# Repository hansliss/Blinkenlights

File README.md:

# Blinkenlights
65C02 adapter for 6502 socket plus blinkenlights on all address and data lines

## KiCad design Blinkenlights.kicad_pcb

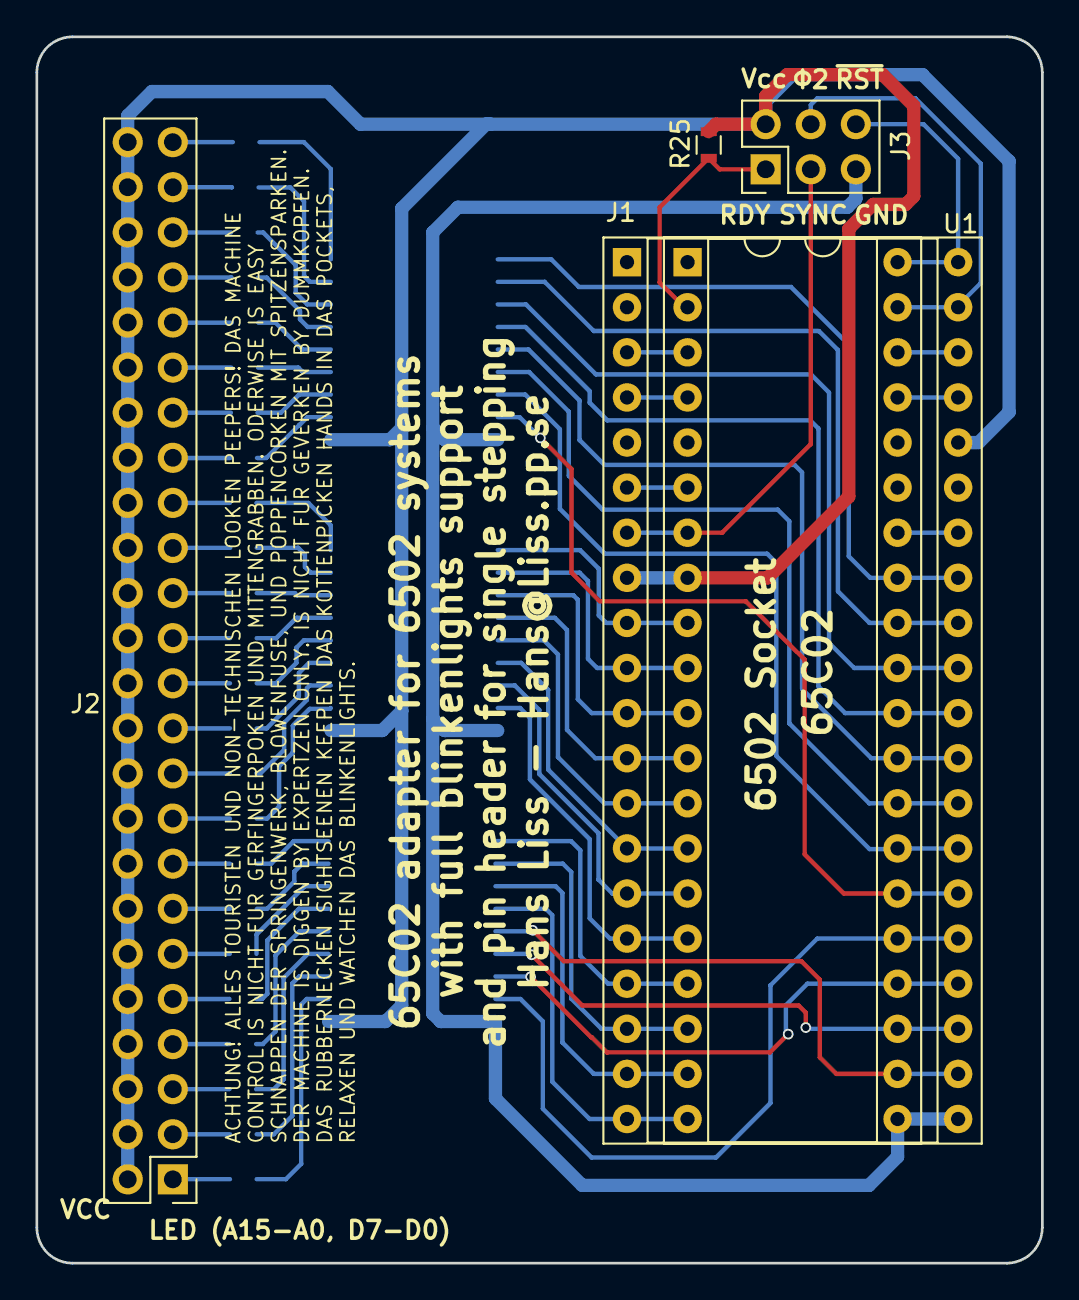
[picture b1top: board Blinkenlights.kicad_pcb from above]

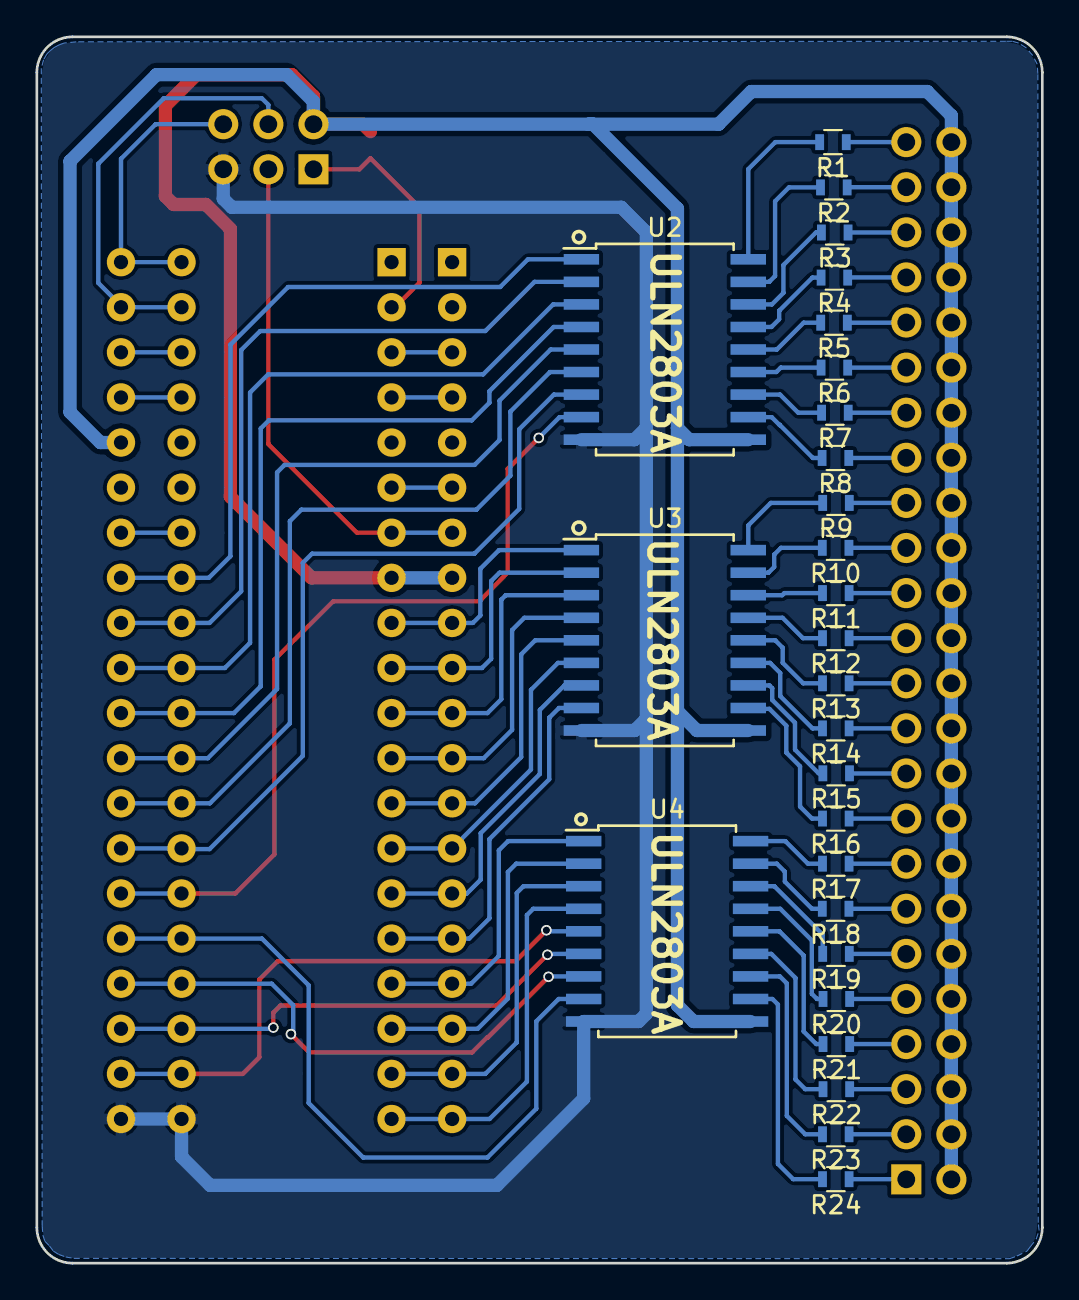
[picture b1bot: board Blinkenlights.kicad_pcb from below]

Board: 2 copper layers, 56.6 x 69.1 mm, 32 parts (27 on the bottom side), 84 nets.

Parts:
J1: 6502_socket; DIP-40_W15.24mm_Socket
J2: Conn_02x24_Odd_Even; Pin_Header_Straight_2x24_Pitch2.54mm
J3: Conn_02x03_Odd_Even; Pin_Header_Straight_2x03_Pitch2.54mm
R1, R2, R3, R4, R5, R6, R7, R8, R9, R10, R11, R12, R13, R14, R15, R16, R17, R18, R19, R20, R21, R22, R23, R24: 4k7; R_0603
R25: 10k; R_0603
U1: WD65C02; DIP-40_W15.24mm_Socket
U2, U3, U4: ULN2803A; SOIC-18W_7.5x11.6mm_Pitch1.27mm

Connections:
/RDY: J3.1, R25.2, U1.2
/SYNC: J1.7, J3.3, U1.7
GND: J1.21, J3.5, U1.21, U2.9, U3.9, U4.9
unnamed: J1.3, U1.3
unnamed: J1.4, U1.4
unnamed: J1.6, U1.6
unnamed: J1.9, U1.9, U3.1
unnamed: J1.10, U1.10, U3.2
unnamed: J1.11, U1.11, U3.3
unnamed: J1.12, U1.12, U3.4
unnamed: J1.13, U1.13, U3.5
unnamed: J1.14, U1.14, U3.6
unnamed: J1.15, U1.15, U3.7
unnamed: J1.16, U1.16, U3.8
unnamed: J1.17, U1.17, U4.1
unnamed: J1.18, U1.18, U4.2
unnamed: J1.19, U1.19, U4.3
unnamed: J1.20, U1.20, U4.4
unnamed: J1.22, U1.22, U4.5
unnamed: J1.23, U1.23, U4.6
unnamed: J1.24, U1.24, U4.7
unnamed: J1.25, U1.25, U4.8
unnamed: J1.26, U1.26, U2.8
unnamed: J1.27, U1.27, U2.7
unnamed: J1.28, U1.28, U2.6
unnamed: J1.29, U1.29, U2.5
unnamed: J1.30, U1.30, U2.4
unnamed: J1.31, U1.31, U2.3
unnamed: J1.32, U1.32, U2.2
unnamed: J1.33, U1.33, U2.1
unnamed: J1.34, U1.34
unnamed: J1.37, U1.37
unnamed: J1.38, U1.38
unnamed: J1.39, J3.4, U1.39
unnamed: J1.40, J3.6, U1.40
unnamed: J2.1, R24.1
unnamed: J2.3, R23.1
unnamed: J2.5, R22.1
unnamed: J2.7, R21.1
unnamed: J2.9, R20.1
unnamed: J2.11, R19.1
unnamed: J2.13, R18.1
unnamed: J2.15, R17.1
unnamed: J2.17, R16.1
unnamed: J2.19, R15.1
unnamed: J2.21, R14.1
unnamed: J2.23, R13.1
unnamed: J2.25, R12.1
unnamed: J2.27, R11.1
unnamed: J2.29, R10.1
unnamed: J2.31, R9.1
unnamed: J2.33, R8.1
unnamed: J2.35, R7.1
unnamed: J2.37, R6.1
unnamed: J2.39, R5.1
unnamed: J2.41, R4.1
unnamed: J2.43, R3.1
unnamed: J2.45, R2.1
unnamed: J2.47, R1.1
unnamed: R1.2, U2.18
unnamed: R2.2, U2.17
unnamed: R3.2, U2.16
unnamed: R4.2, U2.15
unnamed: R5.2, U2.14
unnamed: R6.2, U2.13
unnamed: R7.2, U2.12
unnamed: R8.2, U2.11
unnamed: R9.2, U3.18
unnamed: R10.2, U3.17
unnamed: R11.2, U3.16
unnamed: R12.2, U3.15
unnamed: R13.2, U3.14
unnamed: R14.2, U3.13
unnamed: R15.2, U3.12
unnamed: R16.2, U3.11
unnamed: R17.2, U4.18
unnamed: R18.2, U4.17
unnamed: R19.2, U4.16
unnamed: R20.2, U4.15
unnamed: R21.2, U4.14
unnamed: R22.2, U4.13
unnamed: R23.2, U4.12
unnamed: R24.2, U4.11
VCC: J1.8, J2.2, J2.4, J2.6, J2.8, J2.10, J2.12, J2.14, J2.16, J2.18, J2.20, J2.22, J2.24, J2.26, J2.28, J2.30, J2.32, J2.34, J2.36, J2.38, J2.40, J2.42, J2.44, J2.46, J2.48, J3.2, R25.1, U1.8, U1.36, U2.10, U3.10, U4.10

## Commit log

2018-07-29 Initial import
2018-07-31 Added text to PCB
2018-07-31 Moved text for pin header outside component courtyard
2018-09-15 Improved connector labels
